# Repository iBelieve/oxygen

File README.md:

# Oxygen F7 Flight Controller

## Hardware

- Designed for fixed-wing aircraft
- STM32F756
- MPU-6000 gyroscope & accelerometer
- BMP-388 barometer
- 8 PWM servo outputs
- SRXL2 receiver input
- Qwiic I2C port
- Connector for HC SR-04 ultrasonic distance sensor
- Connector for BN-880Q GPS and compass
- Header with various pins for debugging and experimentation
- USB-C
- microSD slot
- 128MB external flash memory

## Firmware

- Built with Rust
- Very early work-in-progress!!

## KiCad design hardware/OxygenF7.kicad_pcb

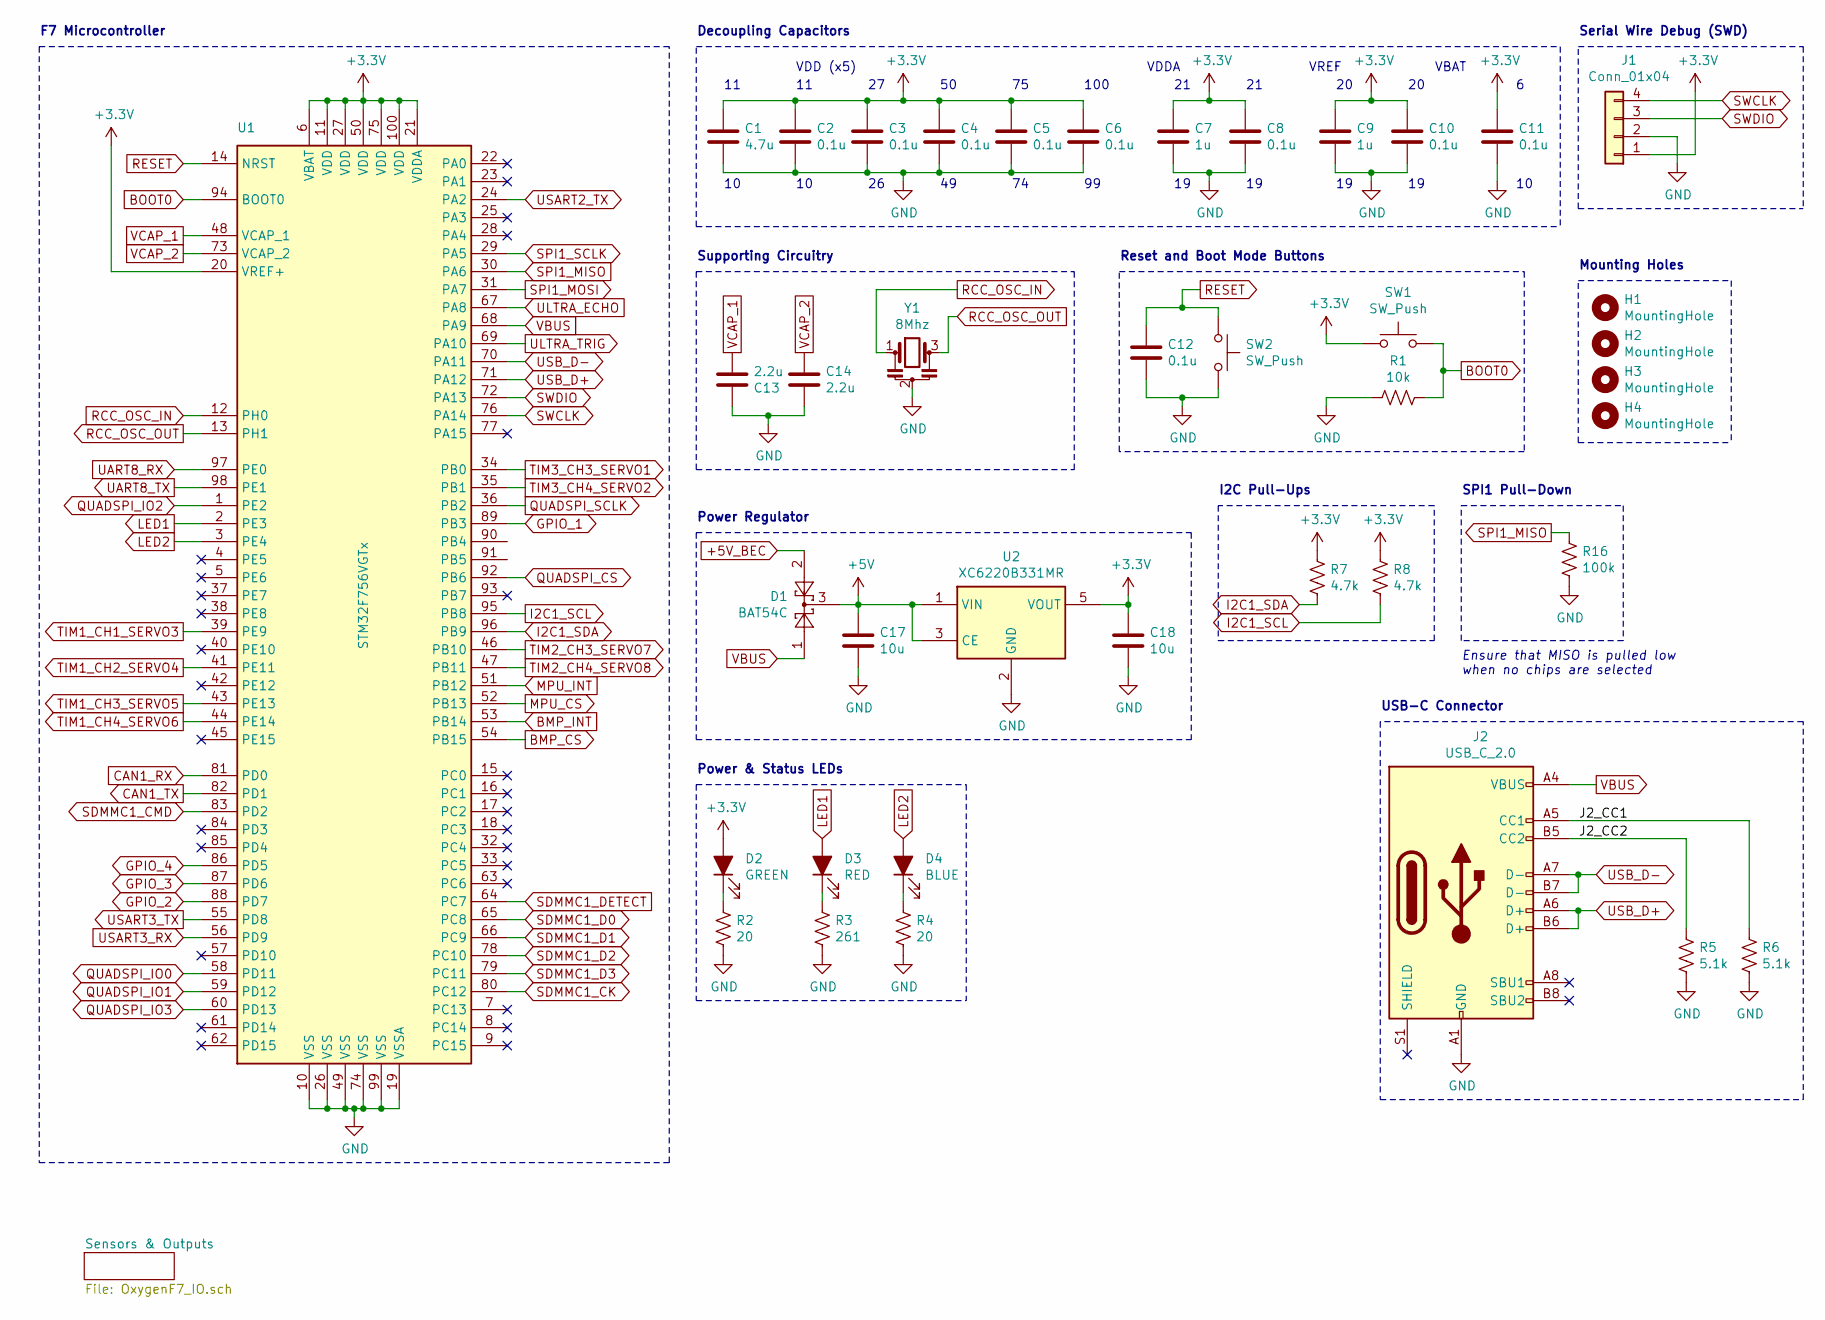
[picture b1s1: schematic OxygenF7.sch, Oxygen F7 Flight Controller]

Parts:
C1: 4.7u; C_0805_2012Metric; Part# CL21B475KPFNNNE
C2, C3, C4, C5, C6, C8, C10, C11, C12: 0.1u; C_0805_2012Metric; Part# CL21B104KBCNNNC‎
C7, C9: 1u; C_0805_2012Metric; Part# CL21B105KOFNNNG
C13, C14: 2.2u; C_0805_2012Metric; Part# CL21B225KPFNNNE
C17, C18: 10u; C_0805_2012Metric; Part# CL21B106KQQNNNG
D1: BAT54C; SOT-23; Part# BAT54CQ-7-F
D2: GREEN; LED_0805_2012Metric; Part# 150080GS75000
D3: RED; LED_0805_2012Metric; Part# 150080RS75000
D4: BLUE; LED_0805_2012Metric; Part# 150080BS75000
H1, H2, H3, H4: MountingHole; MountingHole_3.2mm_M3
J1: Conn_01x04; PinHeader_1x04_P2.54mm_Vertical; Part# PR20204VBNN
J2: USB_C_2.0; USB_C_Receptacle_GCT_USB4085; Part# USB4085-GF-A
R1: 10k; R_0805_2012Metric; Part# RMCF0805FT10K0
R2, R4: 20; R_0805_2012Metric; Part# RMCF0805FT20R0
R3: 261; R_0805_2012Metric; Part# RMCF0805FT261R
R5, R6: 5.1k; R_0805_2012Metric; Part# RMCF0805JT5K10
R7, R8: 4.7k; R_0805_2012Metric; Part# RMCF0805FT4K70
R16: 100k; R_0805_2012Metric; Part# RMCF0805FT100K
SW1, SW2: SW_Push; SW_SPST_TL3342; Part# TL3342F160QG/TR
U1: STM32F756VGTx; LQFP-100_14x14mm_P0.5mm; Part# STM32F756VGT6
U2: XC6220B331MR; SOT-23-5; Part# XC6220B331MR-G
Y1: 8Mhz; Resonator_SMD_muRata_CSTxExxV-3Pin_3.0x1.1mm; Part# CSTNE8M00GH5L000R0

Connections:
+3V3: C1.1, C2.1, C3.1, C4.1, C5.1, C6.1, C7.1, C8.1, C9.1, C10.1, C11.1, C18.1, D2.2 (A), J1.1, R7.1, R8.1, SW1.1, U1.6 (VBAT), U1.11 (VDD), U1.20 (VREF+), U1.21 (VDDA), U1.27 (VDD), U1.50 (VDD), U1.75 (VDD), U1.100 (VDD), U2.5 (VOUT); also elsewhere on the board
+5V: C17.1, D1.3, U2.1 (VIN), U2.3 (CE); also elsewhere on the board
+5V_BEC: D1.2; also elsewhere on the board
/J2_CC1: J2.A5 (CC1), R6.1
/J2_CC2: J2.B5 (CC2), R5.1
BMP_CS: U1.54 (PB15); also elsewhere on the board
BMP_INT: U1.53 (PB14); also elsewhere on the board
BOOT0: R1.2, SW1.2, U1.94 (BOOT0)
CAN1_RX: U1.81 (PD0); also elsewhere on the board
CAN1_TX: U1.82 (PD1); also elsewhere on the board
GND: C1.2, C2.2, C3.2, C4.2, C5.2, C6.2, C7.2, C8.2, C9.2, C10.2, C11.2, C12.2, C13.1, C14.2, C17.2, C18.2, J1.2, J2.A1 (GND), J2.A12 (GND), J2.B1 (GND), J2.B12 (GND), R1.1, R2.2, R3.2, R4.2, R5.2, R6.2, R16.2, SW2.2, U1.10 (VSS), U1.19 (VSSA), U1.26 (VSS), U1.49 (VSS), U1.74 (VSS), U1.99 (VSS), U2.2 (GND), Y1.2; also elsewhere on the board
GPIO_1: U1.89 (PB3); also elsewhere on the board
GPIO_2: U1.88 (PD7); also elsewhere on the board
GPIO_3: U1.87 (PD6); also elsewhere on the board
GPIO_4: U1.86 (PD5); also elsewhere on the board
I2C1_SCL: R8.2, U1.95 (PB8); also elsewhere on the board
I2C1_SDA: R7.2, U1.96 (PB9); also elsewhere on the board
LED1: D3.2 (A), U1.2 (PE3)
LED2: D4.2 (A), U1.3 (PE4)
MPU_CS: U1.52 (PB13); also elsewhere on the board
MPU_INT: U1.51 (PB12); also elsewhere on the board
unnamed: D2.1 (K), R2.1
unnamed: D3.1 (K), R3.1
unnamed: D4.1 (K), R4.1
QUADSPI_CS: U1.92 (PB6); also elsewhere on the board
QUADSPI_IO0: U1.58 (PD11); also elsewhere on the board
QUADSPI_IO1: U1.59 (PD12); also elsewhere on the board
QUADSPI_IO2: U1.1 (PE2); also elsewhere on the board
QUADSPI_IO3: U1.60 (PD13); also elsewhere on the board
QUADSPI_SCLK: U1.36 (PB2); also elsewhere on the board
RCC_OSC_IN: U1.12 (PH0), Y1.1
RCC_OSC_OUT: U1.13 (PH1), Y1.3
RESET: C12.1, SW2.1, U1.14 (NRST)
SDMMC1_CK: U1.80 (PC12); also elsewhere on the board
SDMMC1_CMD: U1.83 (PD2); also elsewhere on the board
SDMMC1_D0: U1.65 (PC8); also elsewhere on the board
SDMMC1_D1: U1.66 (PC9); also elsewhere on the board
SDMMC1_D2: U1.78 (PC10); also elsewhere on the board
SDMMC1_D3: U1.79 (PC11); also elsewhere on the board
SDMMC1_DETECT: U1.64 (PC7); also elsewhere on the board
SPI1_MISO: R16.1, U1.30 (PA6); also elsewhere on the board
SPI1_MOSI: U1.31 (PA7); also elsewhere on the board
SPI1_SCLK: U1.29 (PA5); also elsewhere on the board
SWCLK: J1.4, U1.76 (PA14)
SWDIO: J1.3, U1.72 (PA13)
TIM1_CH1_SERVO3: U1.39 (PE9); also elsewhere on the board
TIM1_CH2_SERVO4: U1.41 (PE11); also elsewhere on the board
TIM1_CH3_SERVO5: U1.43 (PE13); also elsewhere on the board
TIM1_CH4_SERVO6: U1.44 (PE14); also elsewhere on the board
TIM2_CH3_SERVO7: U1.46 (PB10); also elsewhere on the board
TIM2_CH4_SERVO8: U1.47 (PB11); also elsewhere on the board
TIM3_CH3_SERVO1: U1.34 (PB0); also elsewhere on the board
TIM3_CH4_SERVO2: U1.35 (PB1); also elsewhere on the board
UART8_RX: U1.97 (PE0); also elsewhere on the board
UART8_TX: U1.98 (PE1); also elsewhere on the board
ULTRA_ECHO: U1.67 (PA8); also elsewhere on the board
ULTRA_TRIG: U1.69 (PA10); also elsewhere on the board
USART2_TX: U1.24 (PA2); also elsewhere on the board
USART3_RX: U1.56 (PD9); also elsewhere on the board
USART3_TX: U1.55 (PD8); also elsewhere on the board
USB_D+: J2.A6 (D+), J2.B6 (D+), U1.71 (PA12)
USB_D-: J2.A7 (D-), J2.B7 (D-), U1.70 (PA11)
VBUS: D1.1, J2.A4 (VBUS), J2.A9 (VBUS), J2.B4 (VBUS), J2.B9 (VBUS), U1.68 (PA9)
VCAP_1: C13.2, U1.48 (VCAP_1)
VCAP_2: C14.1, U1.73 (VCAP_2)

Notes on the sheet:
Decoupling Capacitors
VDD (x5)
VDDA
F7 Microcontroller
VBAT
100
USB-C Connector
Power & Status LEDs
Supporting Circuitry
Power Regulator
Serial Wire Debug (SWD)
VREF
Mounting Holes
Reset and Boot Mode Buttons
I2C Pull-Ups
SPI1 Pull-Down
Ensure that MISO is pulled low when no chips are selected

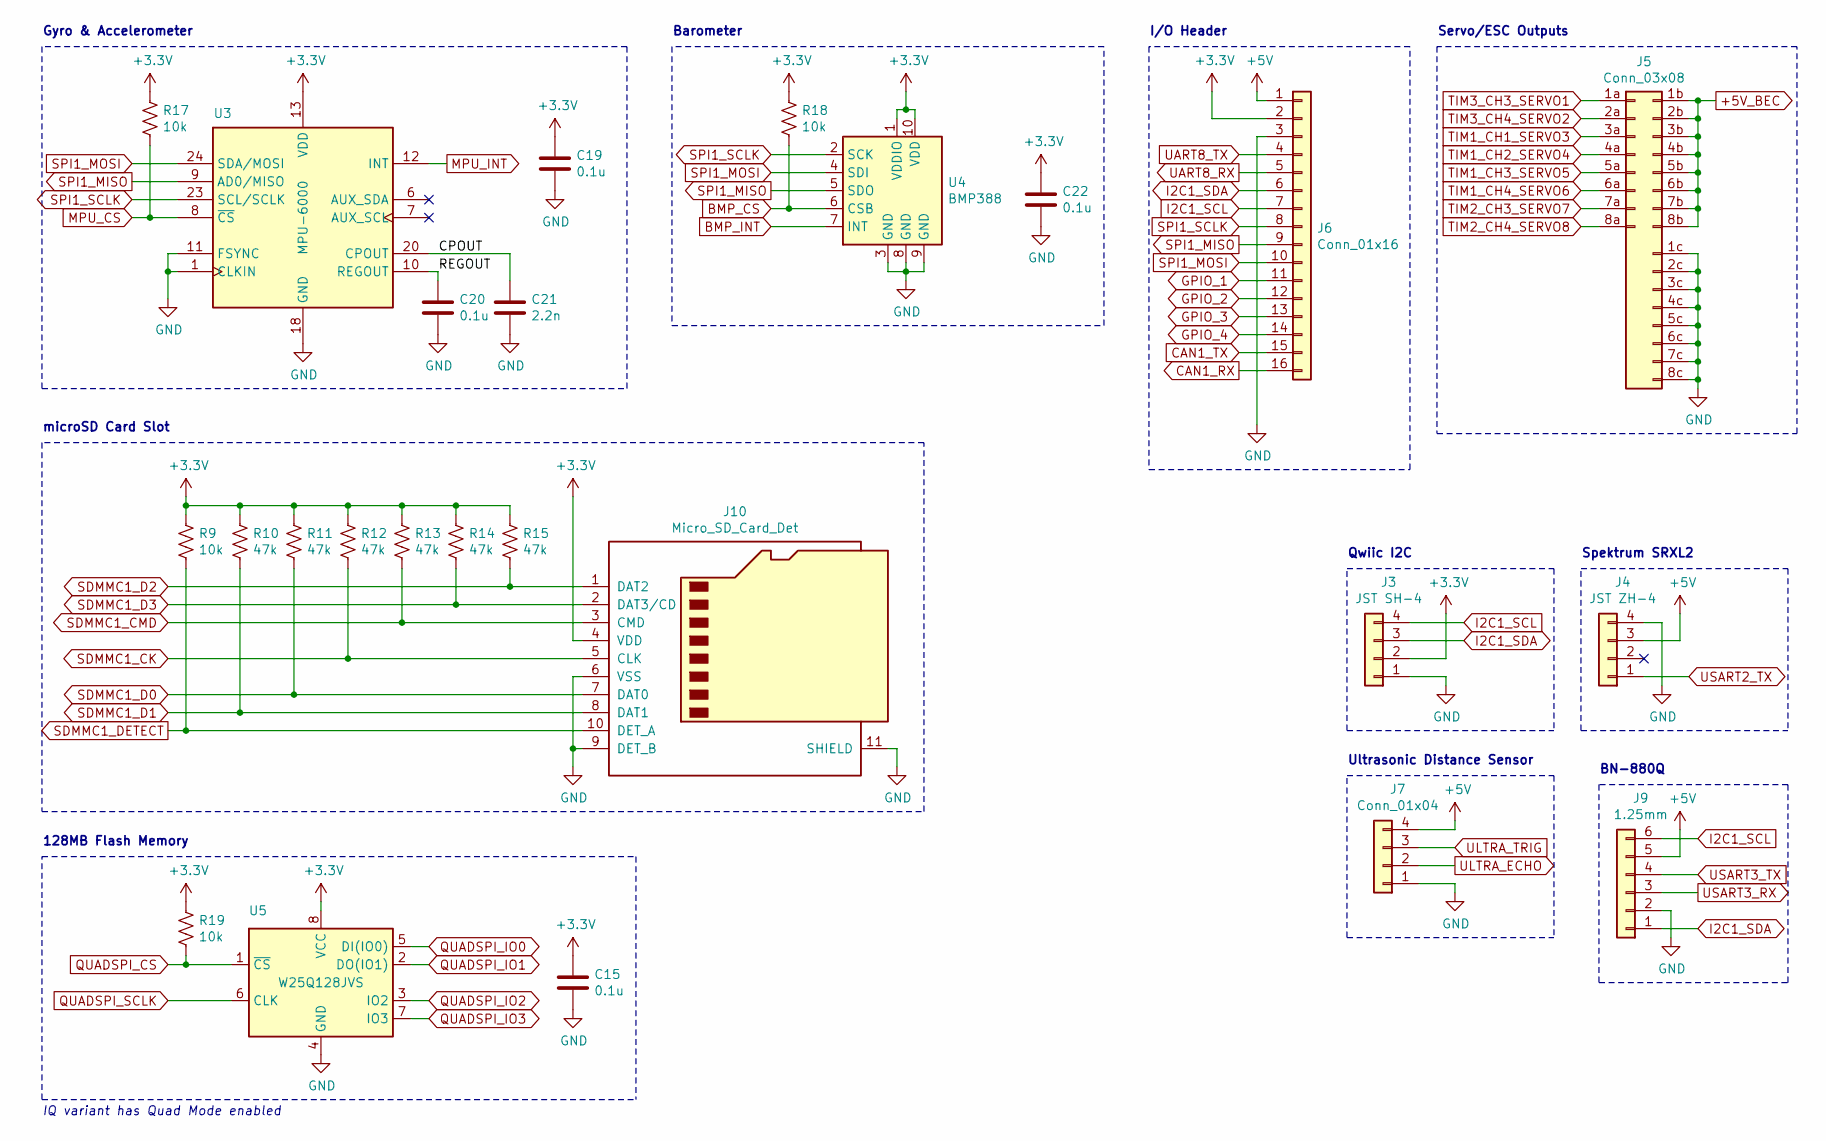
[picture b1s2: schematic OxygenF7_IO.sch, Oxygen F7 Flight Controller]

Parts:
C15, C19, C20, C22: 0.1u; C_0805_2012Metric; Part# CL21B104KBCNNNC‎
C21: 2.2n; C_0805_2012Metric; Part# CL21B222KBANNNC
J3: JST SH-4; JST_SH_SM04B-SRSS-TB_1x04-1MP_P1.00mm_Horizontal; Part# SM04B-SRSS-TB(LF)(SN)
J4: JST ZH-4; JST_ZH_B4B-ZR_1x04_P1.50mm_Vertical; Part# B4B-ZR-SM4-TF(LF)(SN)
J5: Conn_03x08; PinHeader_08x03_P2.54mm_Vertical; Part# PR20208VBNN:3
J6: Conn_01x16; PinHeader_1x16_P2.54mm_Vertical; Part# 61301611121
J7: Conn_01x04; PinHeader_1x04_P2.54mm_Vertical; Part# PR20204VBNN
J9: 1.25mm; 10114830-10106LF_P1.25mm_Horizontal; Part# 10114830-10106LF
J10: Micro_SD_Card_Det; microSD_HC_Hirose_DM3BT-DSF-PEJS; Part# DM3BT-DSF-PEJS
R9, R17, R18, R19: 10k; R_0805_2012Metric; Part# RMCF0805FT10K0
R10, R11, R12, R13, R14, R15: 47k; R_0805_2012Metric; Part# RMCF0805JT47K0
U3: MPU-6000; InvenSense_QFN-24_4x4mm_P0.5mm; Part# MPU-6000
U4: BMP388; LGA-10_2x2mm_P0.5mm; Part# BMP388
U5: W25Q128JVS; SOIC-8_5.23x5.23mm_P1.27mm; Part# W25Q128JVSIQ

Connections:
+3V3: C15.1, C19.1, C22.1, J3.2, J6.2, J10.4 (VDD), R9.1, R10.1, R11.1, R12.1, R13.1, R14.1, R15.1, R17.1, R18.1, R19.1, U3.13 (VDD), U4.1 (VDDIO), U4.10 (VDD), U5.8 (VCC); also elsewhere on the board
+5V: J4.3, J6.1, J7.4, J9.5; also elsewhere on the board
+5V_BEC: J5.1b, J5.2b, J5.3b, J5.4b, J5.5b, J5.6b, J5.7b, J5.8b; also elsewhere on the board
/Sensors & Outputs/CPOUT: C21.1, U3.20 (CPOUT)
/Sensors & Outputs/REGOUT: C20.1, U3.10 (REGOUT)
BMP_CS: R18.2, U4.6 (CSB); also elsewhere on the board
BMP_INT: U4.7 (INT); also elsewhere on the board
CAN1_RX: J6.16; also elsewhere on the board
CAN1_TX: J6.15; also elsewhere on the board
GND: C15.2, C19.2, C20.2, C21.2, C22.2, J3.1, J4.4, J5.1c, J5.2c, J5.3c, J5.4c, J5.5c, J5.6c, J5.7c, J5.8c, J6.3, J7.1, J9.2, J10.6 (VSS), J10.9 (DET_B), J10.11 (SHIELD), U3.1 (CLKIN), U3.11 (FSYNC), U3.18 (GND), U4.3 (GND), U4.8 (GND), U4.9 (GND), U5.4 (GND); also elsewhere on the board
GPIO_1: J6.11; also elsewhere on the board
GPIO_2: J6.12; also elsewhere on the board
GPIO_3: J6.13; also elsewhere on the board
GPIO_4: J6.14; also elsewhere on the board
I2C1_SCL: J3.4, J6.7, J9.6; also elsewhere on the board
I2C1_SDA: J3.3, J6.6, J9.1; also elsewhere on the board
MPU_CS: R17.2, U3.8 (~CS); also elsewhere on the board
MPU_INT: U3.12 (INT); also elsewhere on the board
QUADSPI_CS: R19.2, U5.1 (~CS); also elsewhere on the board
QUADSPI_IO0: U5.5 (DI(IO0)); also elsewhere on the board
QUADSPI_IO1: U5.2 (DO(IO1)); also elsewhere on the board
QUADSPI_IO2: U5.3 (IO2); also elsewhere on the board
QUADSPI_IO3: U5.7 (IO3); also elsewhere on the board
QUADSPI_SCLK: U5.6 (CLK); also elsewhere on the board
SDMMC1_CK: J10.5 (CLK), R12.2; also elsewhere on the board
SDMMC1_CMD: J10.3 (CMD), R13.2; also elsewhere on the board
SDMMC1_D0: J10.7 (DAT0), R11.2; also elsewhere on the board
SDMMC1_D1: J10.8 (DAT1), R10.2; also elsewhere on the board
SDMMC1_D2: J10.1 (DAT2), R15.2; also elsewhere on the board
SDMMC1_D3: J10.2 (DAT3/CD), R14.2; also elsewhere on the board
SDMMC1_DETECT: J10.10 (DET_A), R9.2; also elsewhere on the board
SPI1_MISO: J6.9, U3.9 (AD0/MISO), U4.5 (SDO); also elsewhere on the board
SPI1_MOSI: J6.10, U3.24 (SDA/MOSI), U4.4 (SDI); also elsewhere on the board
SPI1_SCLK: J6.8, U3.23 (SCL/SCLK), U4.2 (SCK); also elsewhere on the board
TIM1_CH1_SERVO3: J5.3a; also elsewhere on the board
TIM1_CH2_SERVO4: J5.4a; also elsewhere on the board
TIM1_CH3_SERVO5: J5.5a; also elsewhere on the board
TIM1_CH4_SERVO6: J5.6a; also elsewhere on the board
TIM2_CH3_SERVO7: J5.7a; also elsewhere on the board
TIM2_CH4_SERVO8: J5.8a; also elsewhere on the board
TIM3_CH3_SERVO1: J5.1a; also elsewhere on the board
TIM3_CH4_SERVO2: J5.2a; also elsewhere on the board
UART8_RX: J6.5; also elsewhere on the board
UART8_TX: J6.4; also elsewhere on the board
ULTRA_ECHO: J7.2; also elsewhere on the board
ULTRA_TRIG: J7.3; also elsewhere on the board
USART2_TX: J4.1; also elsewhere on the board
USART3_RX: J9.3; also elsewhere on the board
USART3_TX: J9.4; also elsewhere on the board

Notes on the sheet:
Qwiic I2C
Spektrum SRXL2
Ultrasonic Distance Sensor
Barometer
Gyro & Accelerometer
I/O Header
microSD Card Slot
Servo/ESC Outputs
BN-880Q
128MB Flash Memory
IQ variant has Quad Mode enabled

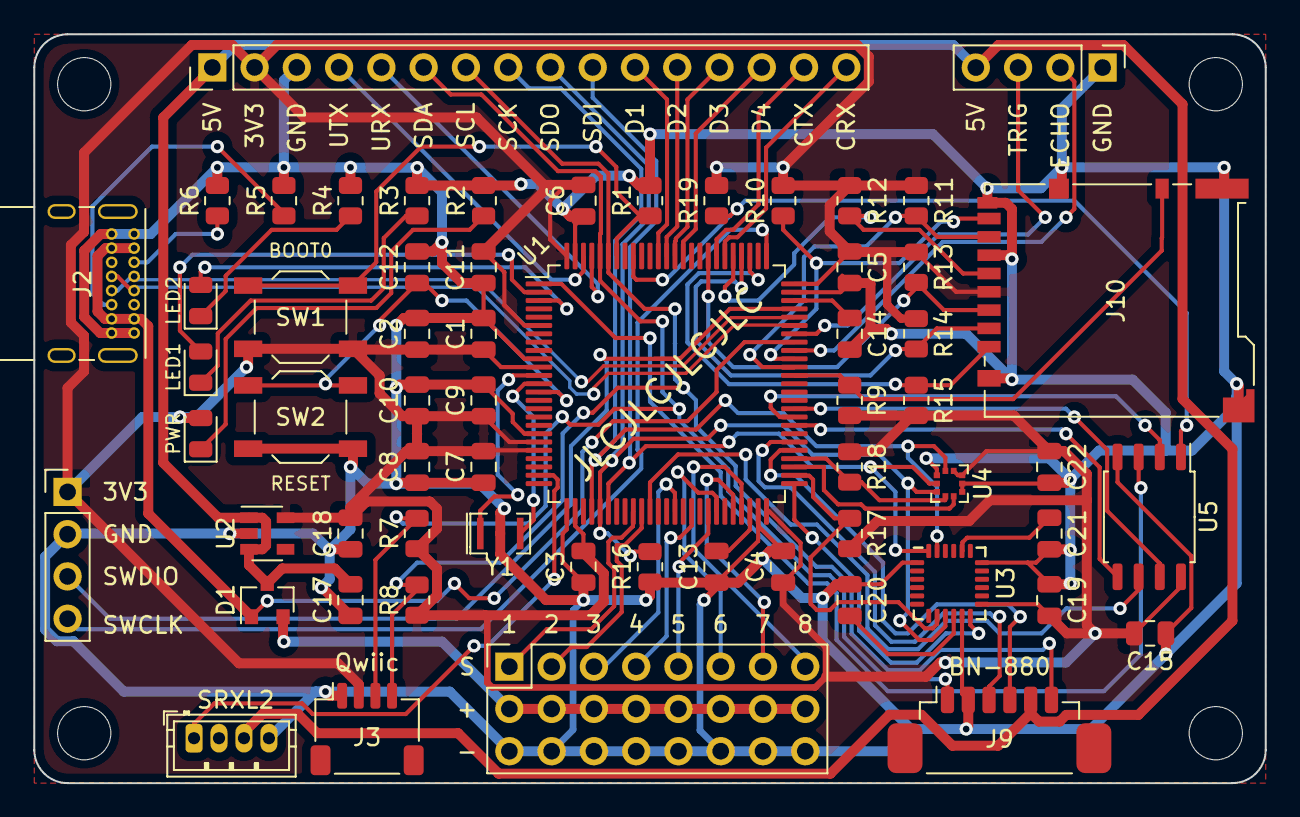
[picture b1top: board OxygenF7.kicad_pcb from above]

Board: 2 copper layers, 74.0 x 45.0 mm, 65 parts (0 on the bottom side), 67 nets.

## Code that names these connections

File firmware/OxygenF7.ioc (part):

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Mcu.Name=STM32F765V(G-I)Tx
Mcu.Package=LQFP100
Mcu.UserName=STM32F765VITx
PA11.Mode=Device_Only
PA11.Signal=USB_OTG_FS_DM
PA12.Mode=Device_Only
PA12.Signal=USB_OTG_FS_DP
PA13.Mode=Serial_Wire
PA13.Signal=SYS_JTMS-SWDIO
PA14.Mode=Serial_Wire
PA14.Signal=SYS_JTCK-SWCLK
PA2.Mode=Asynchronous
PA2.Signal=USART2_TX
PA3.Mode=Asynchronous
PA3.Signal=USART2_RX
PA5.Mode=Full_Duplex_Master
PA5.Signal=SPI1_SCK
PA6.Mode=Full_Duplex_Master
PA6.Signal=SPI1_MISO
PA7.Mode=Full_Duplex_Master
PA7.Signal=SPI1_MOSI
PA9.Mode=Activate_VBUS
PA9.Signal=USB_OTG_FS_VBUS
PB0.Signal=S_TIM3_CH3
PB1.Signal=S_TIM3_CH4
PB10.Signal=S_TIM2_CH3
PB11.Signal=S_TIM2_CH4
PB12.Signal=GPXTI12
PB13.Signal=GPXTI13
PB14.Mode=Half_duplex(single_wire_mode)
PB14.Signal=USART1_TX
PB6.Mode=I2C
PB6.Signal=I2C1_SCL
PB7.Mode=I2C
PB7.Signal=I2C1_SDA
PB8.Mode=Asynchronous
PB8.Signal=UART5_RX
PB9.Mode=Asynchronous
PB9.Signal=UART5_TX
PC0.GPIOParameters=GPIO_Label
PC0.GPIO_Label=MPU_CS
PC0.Signal=GPIO_Output
PC1.GPIOParameters=GPIO_Label
PC1.GPIO_Label=MPU_INT
PC1.Signal=GPIO_Input
PC10.Mode=SD_4_bits_Wide_bus
PC10.Signal=SDMMC1_D2
PC11.Mode=SD_4_bits_Wide_bus
PC11.Signal=SDMMC1_D3
PC12.Mode=SD_4_bits_Wide_bus
PC12.Signal=SDMMC1_CK
PC2.GPIOParameters=GPIO_Label
PC2.GPIO_Label=BMP_CS
PC2.Signal=GPIO_Output
PC3.GPIOParameters=GPIO_Label
PC3.GPIO_Label=BMP_INT
PC3.Signal=GPIO_Input
PC4.GPIOParameters=GPIO_Label
PC4.GPIO_Label=ULTRA_TRIG
PC4.Signal=GPIO_Output
PC5.GPIOParameters=GPIO_Label
PC5.GPIO_Label=ULTRA_ECHO
PC5.Signal=GPIO_Input
PC7.GPIOParameters=GPIO_Label
PC7.GPIO_Label=SDMMC1_DETECT
PC7.Signal=GPIO_Input
PC8.Mode=SD_4_bits_Wide_bus
PC8.Signal=SDMMC1_D0
PC9.Mode=SD_4_bits_Wide_bus
PC9.Signal=SDMMC1_D1
PD0.Mode=CAN_Activate
PD0.Signal=CAN1_RX
PD1.Mode=CAN_Activate
PD1.Signal=CAN1_TX
PD10.Signal=GPXTI10
PD11.Signal=GPXTI11
PD14.Signal=GPXTI14
PD2.Mode=SD_4_bits_Wide_bus
PD2.Signal=SDMMC1_CMD
PE0.GPIOParameters=GPIO_Label
PE0.GPIO_Label=GPIO_1
PE0.Signal=GPIO_Input
PE1.GPIOParameters=GPIO_Label
PE1.GPIO_Label=GPIO_2
PE1.Signal=GPIO_Input
PE11.Signal=S_TIM1_CH2
PE13.Signal=S_TIM1_CH3
PE14.Signal=S_TIM1_CH4
PE2.GPIOParameters=GPIO_Label
PE2.GPIO_Label=GPIO_3
PE2.Signal=GPIO_Input
PE3.GPIOParameters=GPIO_Label
PE3.GPIO_Label=GPIO_4
PE3.Signal=GPIO_Input
PE9.Signal=S_TIM1_CH1
PH0/OSC_IN.Mode=HSE-External-Oscillator
PH0/OSC_IN.Signal=RCC_OSC_IN
PH1/OSC_OUT.Mode=HSE-External-Oscillator
PH1/OSC_OUT.Signal=RCC_OSC_OUT
RCC.HSE_VALUE=8000000
board=custom

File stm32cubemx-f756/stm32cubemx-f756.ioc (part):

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Mcu.Name=STM32F756VGTx
Mcu.Package=LQFP100
Mcu.UserName=STM32F756VGTx
PA11.Mode=Device_Only
PA11.Signal=USB_OTG_FS_DM
PA12.Mode=Device_Only
PA12.Signal=USB_OTG_FS_DP
PA13.Mode=Serial_Wire
PA13.Signal=SYS_JTMS-SWDIO
PA14.Mode=Serial_Wire
PA14.Signal=SYS_JTCK-SWCLK
PA5.Mode=Full_Duplex_Master
PA5.Signal=SPI1_SCK
PA6.Mode=Full_Duplex_Master
PA6.Signal=SPI1_MISO
PA7.Mode=Full_Duplex_Master
PA7.Signal=SPI1_MOSI
PA9.Mode=Activate_VBUS
PA9.Signal=USB_OTG_FS_VBUS
PB10.Mode=Full_Duplex_Master
PB10.Signal=SPI2_SCK
PB2.Mode=Single Bank 1
PB2.Signal=QUADSPI_CLK
PB6.Mode=Single Bank 1
PB6.Signal=QUADSPI_BK1_NCS
PB8.Mode=I2C
PB8.Signal=I2C1_SCL
PB9.Mode=I2C
PB9.Signal=I2C1_SDA
PC1.Mode=Full_Duplex_Master
PC1.Signal=SPI2_MOSI
PC10.Mode=SD_4_bits_Wide_bus
PC10.Signal=SDMMC1_D2
PC11.Mode=SD_4_bits_Wide_bus
PC11.Signal=SDMMC1_D3
PC12.Mode=SD_4_bits_Wide_bus
PC12.Signal=SDMMC1_CK
PC2.Mode=Full_Duplex_Master
PC2.Signal=SPI2_MISO
PC8.Mode=SD_4_bits_Wide_bus
PC8.Signal=SDMMC1_D0
PC9.Mode=SD_4_bits_Wide_bus
PC9.Signal=SDMMC1_D1
PD0.Mode=CAN_Activate
PD0.Signal=CAN1_RX
PD1.Mode=CAN_Activate
PD1.Signal=CAN1_TX
PD11.Mode=Single Bank 1
PD11.Signal=QUADSPI_BK1_IO0
PD12.Mode=Single Bank 1
PD12.Signal=QUADSPI_BK1_IO1
PD13.Mode=Single Bank 1
PD13.Signal=QUADSPI_BK1_IO3
PD2.Mode=SD_4_bits_Wide_bus
PD2.Signal=SDMMC1_CMD
PE0.Mode=Asynchronous
PE0.Signal=UART8_RX
PE1.Mode=Asynchronous
PE1.Signal=UART8_TX
PE12.Mode=Full_Duplex_Master
PE12.Signal=SPI4_SCK
PE2.Mode=Single Bank 1
PE2.Signal=QUADSPI_BK1_IO2
PE5.Mode=Full_Duplex_Master
PE5.Signal=SPI4_MISO
PE6.Mode=Full_Duplex_Master
PE6.Signal=SPI4_MOSI
PH0/OSC_IN.Mode=HSE-External-Oscillator
PH0/OSC_IN.Signal=RCC_OSC_IN
PH1/OSC_OUT.Mode=HSE-External-Oscillator
PH1/OSC_OUT.Signal=RCC_OSC_OUT
RCC.HSE_VALUE=8000000
RCC.SYSCLKFreq_VALUE=216000000
RCC.SYSCLKSource=RCC_SYSCLKSOURCE_PLLCLK
board=custom

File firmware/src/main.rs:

// #![deny(unsafe_code)]
#![no_main]
#![no_std]

extern crate panic_rtt_target;

// mod boards;
// mod device;
// mod mpu6000;
mod clock;
mod drivers;

use embedded_hal::blocking::delay::DelayMs;
// use mpu6000::{
//     bus::{Bus, SpiBus},
//     registers::{AccelerometerSensitive, GyroSensitive},
//     MPU6000,
// };
use crate::clock::SysClock;
use crate::drivers::Servos;
use embedded_time::Clock;
use rtic::app;
use rtt_target::{rprintln, rtt_init_print};
use stm32f7xx_hal::gpio::gpioa::{PA10, PA8};
use stm32f7xx_hal::gpio::{Floating, Input, Output, PushPull};
use stm32f7xx_hal::pac::{EXTI, TIM1, TIM2, TIM3, TIM4};
use stm32f7xx_hal::pwm::{PwmChannels, C1, C2, C3, C4};
use stm32f7xx_hal::timer::Event;
use stm32f7xx_hal::{
    delay::Delay,
    gpio::{self, Edge, ExtiPin},
    i2c::{self, I2c},
    pac,
    prelude::*,
    pwm,
    rcc::{HSEClock, HSEClockMode},
    spi::{self, Spi},
    time::KiloHertz,
    timer::Timer,
};

type I2C1 = I2c<
    pac::I2C1,
    gpio::gpiob::PB8<gpio::Alternate<gpio::AF4>>,
    gpio::gpiob::PB9<gpio::Alternate<gpio::AF4>>,
>;

type SPI1 = Spi<
    pac::SPI1,
    (
        gpio::gpioa::PA5<gpio::Alternate<gpio::AF5>>,
        gpio::gpioa::PA6<gpio::Alternate<gpio::AF5>>,
        gpio::gpioa::PA7<gpio::Alternate<gpio::AF5>>,
    ),
    spi::Enabled<u8>,
>;

type TriggerPin = PA10<Output<PushPull>>;
type EchoPin = PA8<Input<Floating>>;
type HcSr04 = crate::drivers::HcSr04<TriggerPin>;

#[app(device = stm32f7xx_hal::pac, peripherals = true)]
const APP: () = {
    struct Resources {
        delay: Delay,
        servos: Servos,
        clock: SysClock,
        hcsr04_timer: Timer<TIM4>,
        hcsr04: HcSr04,
        echo_pin: EchoPin,
    }

    #[init]
    fn init(ctx: init::Context) -> init::LateResources {
        rtt_init_print!();
        rprintln!("Welcome to Oxygen F7");

        let core: cortex_m::Peripherals = ctx.core;
        let mut device: stm32f7xx_hal::pac::Peripherals = ctx.device;

        let gpioa = device.GPIOA.split();
        let gpiob = device.GPIOB.split();
        let gpioe = device.GPIOE.split();

        // LED pins
        let mut led1 = gpioe.pe2.into_push_pull_output();
        let mut led2 = gpioe.pe3.into_push_pull_output();

        // Set LED pins to high to indicate flight controller is working
        led1.set_high().unwrap();
        led2.set_high().unwrap();

        // MPU Interrupt pin
        let mut mpu_int = gpiob.pb12.into_floating_input();
        mpu_int.make_interrupt_source(&mut device.SYSCFG, &mut device.RCC);
        mpu_int.trigger_on_edge(&mut device.EXTI, Edge::Rising);
        mpu_int.enable_interrupt(&mut device.EXTI);

        // BMP Interrupt pin
        let mut bmp_int = gpiob.pb14.into_floating_input();
        bmp_int.make_interrupt_source(&mut device.SYSCFG, &mut device.RCC);
        bmp_int.trigger_on_edge(&mut device.EXTI, Edge::Rising);
        bmp_int.enable_interrupt(&mut device.EXTI);

        // MPU and BMP chip select pins
        let mut mpu_cs = gpiob.pb13.into_push_pull_output();
        let mut bmp_cs = gpiob.pb15.into_push_pull_output();

        // Set CS pins to high (disabled) initially
        mpu_cs.set_high().unwrap();
        bmp_cs.set_high().unwrap();

        // Distance Sensor
        let hcsr04 = HcSr04::new(gpioa.pa10.into_push_pull_output())
            .expect("Unable to initialize HC SR-04 ultrasonic distance sensor");

        let mut echo_pin = gpioa.pa8.into_floating_input();
        echo_pin.make_interrupt_source(&mut device.SYSCFG, &mut device.RCC);
        echo_pin.trigger_on_edge(&mut device.EXTI, Edge::RisingFalling);
        echo_pin.enable_interrupt(&mut device.EXTI);

        // Constrain clocking registers
        let mut rcc = device.RCC.constrain();

        // Configure clock and freeze it
        let clocks = rcc
            .cfgr
            .hse(HSEClock::new(8.mhz(), HSEClockMode::Oscillator))
            .sysclk(216.mhz())
            .freeze();

        // Distance sensor trigger timer
        let mut hcsr04_timer = Timer::tim4(device.TIM4, 10.hz(), clocks, &mut rcc.apb1);
        hcsr04_timer.listen(Event::TimeOut);

        // Monotonic clock
        let clock = SysClock::new(device.TIM5, clocks);

        // Get delay provider
        let mut delay = Delay::new(core.SYST, clocks);

        // Servos!
        let servos = Servos::new(
            clocks,
            device.TIM1,
            device.TIM2,
            device.TIM3,
            gpiob.pb0.into_alternate_af2(),
            gpiob.pb1.into_alternate_af2(),
            gpioe.pe9.into_alternate_af1(),
            gpioe.pe11.into_alternate_af1(),
            gpioe.pe13.into_alternate_af1(),
            gpioe.pe14.into_alternate_af1(),
            gpiob.pb10.into_alternate_af1(),
            gpiob.pb11.into_alternate_af1(),
        );

        // I2C1
        let scl = gpiob.pb8.into_alternate_af4();
        let sda = gpiob.pb9.into_alternate_af4();

        let i2c1 = I2c::i2c1(
            device.I2C1,
            (scl, sda),
            i2c::Mode::standard(400.khz()),
            clocks,
            &mut rcc.apb1,
        );

        let i2c1_shared: &'static _ = shared_bus::new_atomic_check!(I2C1 = i2c1).unwrap();

        // SPI1
        let sck = gpioa.pa5.into_alternate_af5();
        let miso = gpioa.pa6.into_alternate_af5();
        let mosi = gpioa.pa7.into_alternate_af5();

        let spi1 = Spi::new(device.SPI1, (sck, miso, mosi)).enable::<u8>(
            &mut rcc.apb2,             // 108 MHz
            spi::ClockDivider::DIV128, // 108/128 = 0.84Mhz (must be 1MHz or less)
            spi::Mode {
                polarity: spi::Polarity::IdleHigh,
                phase: spi::Phase::CaptureOnSecondTransition,
            },
        );

        let spi1_shared: &'static _ = shared_bus::new_atomic_check!(SPI1 = spi1).unwrap();

        // let spi_bus = SpiBus::new(spi, mpu_ncs, delay);
        // let mut mpu6000 = MPU6000::new(spi_bus);
        // mpu6000.reset(&mut delay).unwrap();
        // mpu6000.wake(&delay).unwrap();
        // mpu6000
        //     .set_accelerometer_sensitive(accelerometer_sensitive!(+/-16g, 2048/LSB))
        //     .unwrap();
        // mpu6000
        //     .set_gyro_sensitive(gyro_sensitive!(+/-2000dps, 16.4LSB/dps))
        //     .unwrap();

        init::LateResources {
            delay,
            clock,
            hcsr04_timer,
            hcsr04,
            echo_pin,
            servos,
        }
    }

    #[task(binds = TIM4, resources = [delay, hcsr04_timer, hcsr04])]
    fn hcsr04_timer(ctx: hcsr04_timer::Context) {
        let delay: &mut Delay = ctx.resources.delay;
        let timer: &mut Timer<TIM4> = ctx.resources.hcsr04_timer;
        let hcsr04: &mut HcSr04 = ctx.resources.hcsr04;

        timer.clear_interrupt(Event::TimeOut);

        hcsr04
            .trigger(delay)
            .expect("Unable to trigger distance reading");
    }

    #[task(binds = EXTI9_5, resources = [clock, echo_pin, hcsr04])]
    fn exti9_5(ctx: exti9_5::Context) {
        let echo_pin: &mut EchoPin = ctx.resources.echo_pin;
        let clock: &mut SysClock = ctx.resources.clock;
        let hcsr04: &mut HcSr04 = ctx.resources.hcsr04;

        let now = clock
            .try_now()
            .expect("Unable to get current time from system clock");

        if echo_pin.check_interrupt() {
            echo_pin.clear_interrupt_pending_bit();

            if echo_pin.is_high().unwrap() {
                hcsr04
                    .on_echo_start(now)
                    .expect("Error handling HC-SR04 echo start");
            } else {
                let dist_mm = hcsr04
                    .on_echo_end(now)
                    .expect("Error handling HC-SR04 echo end");
                rprintln!("Current distance: {}mm", dist_mm);
            }
        } else {
            rprintln!("Unexpected EXTI9_5 interrupt");
        }
    }
};

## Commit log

2021-04-24 Initial project
2021-05-08 Swap out some out-of-stock parts
2021-05-09 Make Sonrise a local symbol library
2021-05-09 Don't ground unused MCU pins and add microSD pull-up resistors
2021-05-09 Add more pull-up/pull-down resistors and 128MB flash memory
2021-05-11 New board layout
2021-05-11 Update clearances to satisfy DRC
2021-05-11 Update resistor values for status LED to use only 5mA
2021-05-11 Small layout tweaks
2021-05-12 Small tweaks
2021-05-15 Initial Rust firmware project
2021-05-16 Initial progress on firmware
2021-05-16 Refactor servo logic into separate module
2021-05-16 Add STM32CubeMX project
2021-05-16 Add screenshot of current board design
2021-05-16 Add README
2021-05-16 Remove old F765-based hardware design
2021-05-16 Rename hardware-f756 to just hardware
2024-05-02 Add photos of the completed PCB
